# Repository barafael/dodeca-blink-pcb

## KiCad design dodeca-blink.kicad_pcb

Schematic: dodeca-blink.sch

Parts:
C1, C2, C3, C4, C5, C6: C; CP_Radial_D10.0mm_P5.00mm
H1, H2, H3, H4: MountingHole; MountingHole_3mm
J1, J2: Conn_02x03_Counter_Clockwise; PinHeader_2x03_P2.54mm_Vertical
J3: Conn_02x01; JST_XH_B2B-XH-AM_1x02_P2.50mm_Vertical
R1, R2, R3, R4, R5, R6: 4,7k; R_Axial_DIN0207_L6.3mm_D2.5mm_P7.62mm_Horizontal
U1, U2: 74HCT125; DIP-14_W7.62mm
U3: ESP32-DEVKITC-32D; MODULE_ESP32-DEVKITC-32D; PARTREV 4
U4: INMP441; inmp441
U5: sdcard_module

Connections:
3v3: U1.1, U4.2 (VDD)
5V: C1.2, C2.2, C3.2, C4.2, C5.2, C6.2, J1.2, J1.4, J1.6, J3.1, U1.19, U2.14, U3.14, U5.2 (SCK)
CLK: U1.28, U5.5 (VCC)
CS: U1.29, U5.6 (GND)
GND: C1.1, C2.1, C3.1, C4.1, C5.1, C6.1, J1.1, J1.3, J1.5, J3.2, U1.14, U1.20, U1.26, U2.1, U2.4, U2.7, U2.10, U2.12, U2.13, U3.1, U3.4, U3.7, U3.10, U3.12, U3.13, U4.1 (GND), U4.4 (L/R), U5.1 (CS)
MIC_SCK: U1.12, U4.6 (SCK)
MISO: U1.27, U5.3 (MOSI)
MOSI: U1.21, U5.4 (MISO)
unnamed: R1.1, U2.3
unnamed: R2.1, U2.6
unnamed: R3.1, U2.8
unnamed: R4.1, U3.3
unnamed: R5.1, U3.6
unnamed: R6.1, U3.8
SD: U1.7, U4.3 (SD)
STRIP1_OUT: J2.1, R1.2
STRIP2_OUT: J2.2, R2.2
STRIP3_OUT: J2.3, R3.2
STRIP4_OUT: J2.4, R4.2
STRIP5_OUT: J2.5, R5.2
STRIP6_OUT: J2.6, R6.2
STRIP_1: U1.15, U2.2
STRIP_2: U1.13, U2.5
STRIP_3: U1.11, U2.9
STRIP_4: U1.10, U3.2
STRIP_5: U1.9, U3.5
STRIP_6: U1.8, U3.9
WS: U1.35, U4.5 (WS)

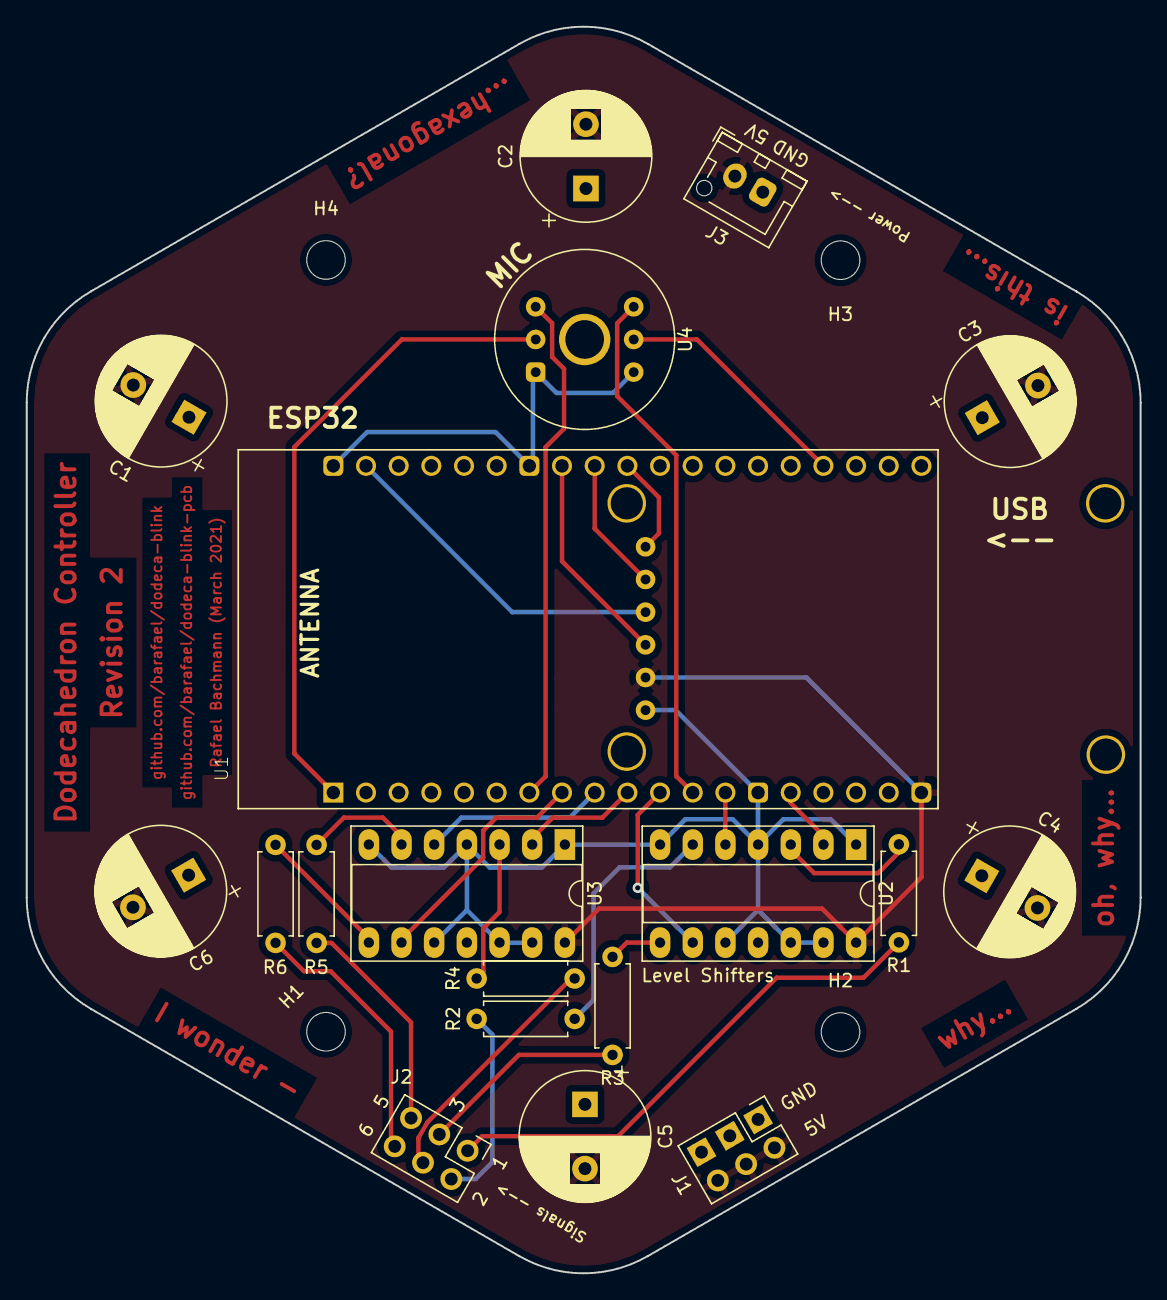
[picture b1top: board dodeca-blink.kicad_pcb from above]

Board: 2 copper layers, 86.6 x 96.9 mm, 24 parts (1 on the bottom side), 28 nets.

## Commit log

2021-03-17 Change pins
    avoid pin 0 and pin 2 on esp32 (these are boot pins)
2021-03-20 Replace pico kit with devkit-v4 from SnapEDA
2021-03-29 Update PCB
2021-04-06 Add micro sd and mic
2021-04-08 Add board render
2021-04-28 Rotate the capacitors
2021-04-29 Minor adjustments
2021-05-07 Use thicker traces
2021-06-13 Fix lib paths
2021-06-13 Rename lamp-base to dodeca-blink finally
2021-06-13 Remove pico footprint
2021-06-13 Fix paths and relax track spacing a little
2021-06-13 Set URLs in .gitmodules to https
2022-06-11 Fix pad outlines for power pins
